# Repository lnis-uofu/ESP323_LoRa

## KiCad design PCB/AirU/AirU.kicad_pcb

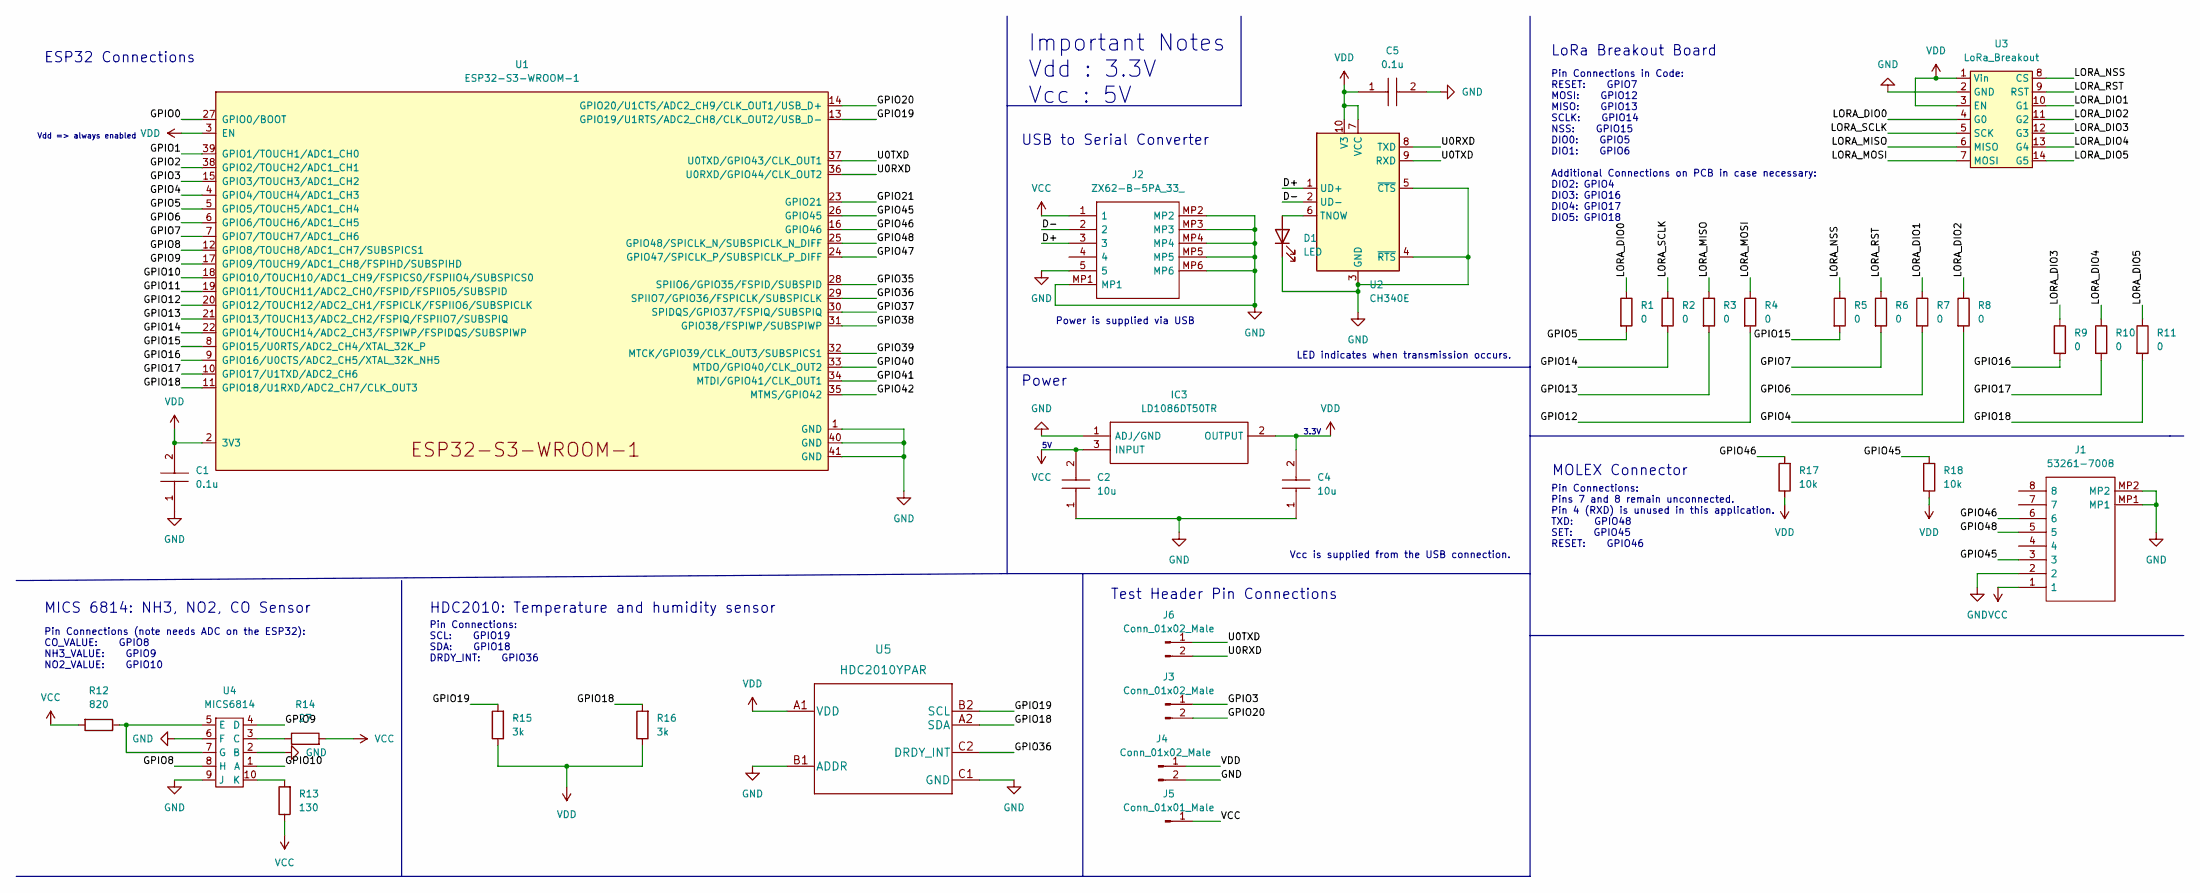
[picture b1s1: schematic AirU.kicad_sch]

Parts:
C1: 0.1u; CAPC1608X94N; Mouser Part Number 581-0603YC105KAT2A
C2, C4: 10u; CAPC1608X90N; Mouser Part Number 581-0603ZD106KAT2A
C5: 0.1u; CAPC1608X90N; Mouser Part Number 581-0603YC104J4T4A
D1: LED; LED_0603_1608Metric
IC3: LD1086DT50TR; LD1086DT33TR; Mouser Part Number 511-LD1086DT50TR
J1: 53261-7008; 532617008; Mouser Part Number 538-53261-7008
J2: ZX62-B-5PA_33_; ZX62B5PA33; Mouser Part Number 798-ZX62-B-5PA33
J3, J4, J6: Conn_01x02_Male; PinHeader_1x02_P2.54mm_Vertical
J5: Conn_01x01_Male; PinHeader_1x01_P2.54mm_Vertical
R1, R2, R3, R4, R5, R6, R7, R8, R9, R10, R11: 0; R_0603_1608Metric
R12: 820; R_0603_1608Metric
R13: 130; R_0603_1608Metric
R14: 27; R_0603_1608Metric
R15, R16: 3k; R_0603_1608Metric
R17, R18: 10k; R_0603_1608Metric
U1: ESP32-S3-WROOM-1
U2: CH340E; MSOP-10_3x3mm_P0.5mm
U3: LoRa_Breakout
U4: MICS6814; PLCC125P750X550X150-16N
U5: HDC2010YPAR

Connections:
/D+: J2.3, U2.1 (UD+)
/D-: J2.2, U2.2 (UD-)
/GPIO0: U1.27 (GPIO0/BOOT)
/GPIO1: U1.39 (GPIO1/TOUCH1/ADC1_CH0)
/GPIO2: U1.38 (GPIO2/TOUCH2/ADC1_CH1)
/GPIO3: J3.1, U1.15 (GPIO3/TOUCH3/ADC1_CH2)
/GPIO4: R8.2, U1.4 (GPIO4/TOUCH4/ADC1_CH3)
/GPIO5: R1.2, U1.5 (GPIO5/TOUCH5/ADC1_CH4)
/GPIO6: R7.2, U1.6 (GPIO6/TOUCH6/ADC1_CH5)
/GPIO7: R6.2, U1.7 (GPIO7/TOUCH7/ADC1_CH6)
/GPIO8: U1.12 (GPIO8/TOUCH8/ADC1_CH7/SUBSPICS1), U4.8 (H)
/GPIO9: U1.17 (GPIO9/TOUCH9/ADC1_CH8/FSPIHD/SUBSPIHD), U4.4 (D)
/GPIO10: U1.18 (GPIO10/TOUCH10/ADC1_CH9/FSPICS0/FSPIIO4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), U4.1 (A)
/GPIO11: U1.19 (GPIO11/TOUCH11/ADC2_CH0/FSPID/FSPIIO5/S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)
/GPIO12: R4.2, U1.20 (GPIO12/TOUCH12/ADC2_CH1/FSPICLK/FSPIIO6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)
/GPIO13: R3.2, U1.21 (GPIO13/TOUCH13/ADC2_CH2/FSPIQ/FSPIIO7/S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)
/GPIO14: R2.2, U1.22 (GPIO14/TOUCH14/ADC2_CH3/FSPIWP/FSPIDQS/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)
/GPIO15: R5.2, U1.8 (GPIO15/U0RTS/ADC2_CH4/XTAL_32K_P)
/GPIO16: R9.2, U1.9 (GPIO16/U0CTS/ADC2_CH5/XTAL_32K_NH5)
/GPIO17: R10.2, U1.10 (GPIO17/U1TXD/ADC2_CH6)
/GPIO18: R11.2, R16.2, U1.11 (GPIO18/U1RXD/ADC2_CH7/CLK_OUT3), U5.A2 (SDA)
/GPIO19: R15.2, U1.13 (GPIO19/U1RTS/ADC2_CH8/CLK_OUT2/USB_D-), U5.B2 (SCL)
/GPIO20: J3.2, U1.14 (GPIO20/U1CTS/ADC2_CH9/CLK_OUT1/USB_D+)
/GPIO21: U1.23 (GPIO21)
/GPIO35: U1.28 (SPIIO6/GPIO35/FSPID/SUBSPID)
/GPIO36: U1.29 (SPIIO7/GPIO36/FSPICLK/SUBSPICLK), U5.C2 (DRDY_INT)
/GPIO37: U1.30 (SPIDQS/GPIO37/FSPIQ/SUBSPIQ)
/GPIO38: U1.31 (GPIO38/FSPIWP/SUBSPIWP)
/GPIO39: U1.32 (MTCK/GPIO39/CLK_OUT3/SUBSPICS1)
/GPIO40: U1.33 (MTDO/GPIO40/CLK_OUT2)
/GPIO41: U1.34 (MTDI/GPIO41/CLK_OUT1)
/GPIO42: U1.35 (MTMS/GPIO42)
/GPIO45: J1.3, R18.2, U1.26 (GPIO45)
/GPIO46: J1.6, R17.2, U1.16 (GPIO46)
/GPIO47: U1.24 (GPIO47/SPICLK_P/SUBSPICLK_P_DIFF)
/GPIO48: J1.5, U1.25 (GPIO48/SPICLK_N/SUBSPICLK_N_DIFF)
/LORA_DIO0: R1.1, U3.4 (G0)
/LORA_DIO1: R7.1, U3.10 (G1)
/LORA_DIO2: R8.1, U3.11 (G2)
/LORA_DIO3: R9.1, U3.12 (G3)
/LORA_DIO4: R10.1, U3.13 (G4)
/LORA_DIO5: R11.1, U3.14 (G5)
/LORA_MISO: R3.1, U3.6 (MISO)
/LORA_MOSI: R4.1, U3.7 (MOSI)
/LORA_NSS: R5.1, U3.8 (CS)
/LORA_RST: R6.1, U3.9 (RST)
/LORA_SCLK: R2.1, U3.5 (SCK)
/U0RXD: J6.2, U1.36 (U0RXD/GPIO44/CLK_OUT2), U2.8 (TXD)
/U0TXD: J6.1, U1.37 (U0TXD/GPIO43/CLK_OUT1), U2.9 (RXD)
GND: C1.1, C2.1, C4.1, C5.2, D1.1 (K), IC3.1 (ADJ/GND), J1.2, J1.MP1, J1.MP2, J2.5, J2.MP1, J2.MP2, J2.MP3, J2.MP4, J2.MP5, J2.MP6, J4.2, U1.1 (GND), U1.40 (GND), U1.41 (GND), U2.3 (GND), U2.4 (~RTS), U2.5 (~CTS), U3.2 (GND), U4.2 (B), U4.6 (F), U4.9 (J), U5.B1 (ADDR), U5.C1 (GND)
unnamed: D1.2 (A), U2.6 (TNOW)
unnamed: R12.1, U4.5 (E), U4.7 (G)
unnamed: R13.2, U4.10 (K)
unnamed: R14.1, U4.3 (C)
VCC: C2.2, IC3.3 (INPUT), J1.1, J2.1, J5.1, R12.2, R13.1, R14.2
VDD: C1.2, C4.2, C5.1, IC3.2 (OUTPUT), J4.1, R15.1, R16.1, R17.1, R18.1, U1.2 (3V3), U1.3 (EN), U2.7 (VCC), U2.10 (V3), U3.1 (Vin), U3.3 (EN), U5.A1 (VDD)

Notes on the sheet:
LoRa Breakout Board
Pin Connections in Code: RESET: GPIO7 MOSI: GPIO12 MISO: GPIO13 SCLK: GPIO14 NSS: GPIO15 DIO0: GPIO5 DIO1: GPIO6 Additional Connections on PCB in case necessary: DIO2: GPIO4 DIO3: GPIO16 DIO4: GPIO17 DIO5: GPIO18
Vcc is supplied from the USB connection.
HDC2010: Temperature and humidity sensor
MOLEX Connector
Pin Connections: SCL: GPIO19 SDA: GPIO18 DRDY_INT: GPIO36
Vdd => always enabled
USB to Serial Converter
LED indicates when transmission occurs.
Important Notes Vdd : 3.3V Vcc : 5V
Test Header Pin Connections
MICS 6814: NH3, NO2, CO Sensor
Pin Connections (note needs ADC on the ESP32): CO_VALUE: GPIO8 NH3_VALUE: GPIO9 NO2_VALUE: GPIO10
Power is supplied via USB
3.3V
ESP32 Connections
Pin Connections: Pins 7 and 8 remain unconnected. Pin 4 (RXD) is unused in this application. TXD: GPIO48 SET: GPIO45 RESET: GPIO46
Power

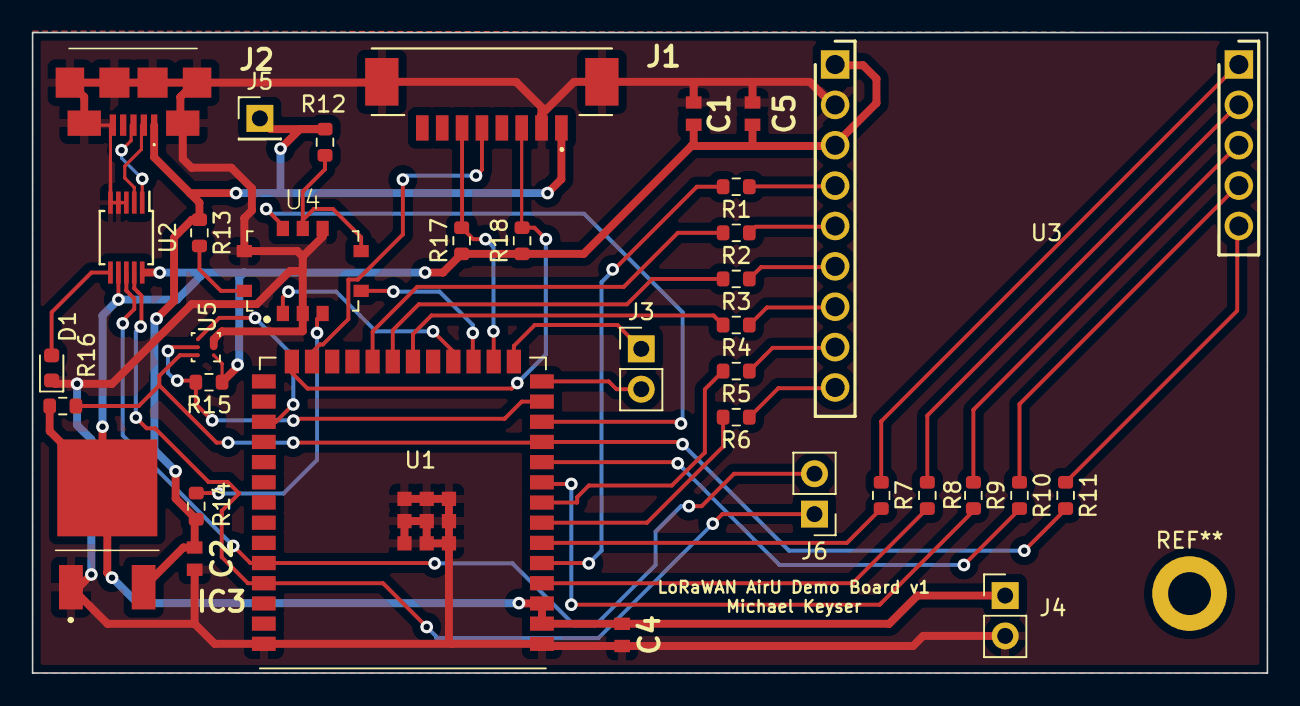
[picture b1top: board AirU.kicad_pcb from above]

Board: 2 copper layers, 77.7 x 40.3 mm, 35 parts (0 on the bottom side), 43 nets.

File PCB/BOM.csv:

"Id";"Designator";"Package";"Quantity";"Designation";"Supplier and ref";
1;"R5,R8,R9,R3,R2,R7,R6,R10,R4,R1,R11";"R_0603_1608Metric";11;"0";;;
2;"R14";"R_0603_1608Metric";1;"27";;;
3;"J6,J4,J3";"PinHeader_1x02_P2.54mm_Vertical";3;"Conn_01x02_Male";;;
4;"U1";"ESP32-S3-WROOM-1";1;"ESP32-S3-WROOM-1";;;
5;"R17,R18";"R_0603_1608Metric";2;"10k";;;
6;"C4,C2";"CAPC1608X90N";2;"10u";;;
7;"U5";"HDC2010YPAR";1;"HDC2010YPAR";;;
8;"R15,R16";"R_0603_1608Metric";2;"3k";;;
9;"D1";"LED_0603_1608Metric";1;"LED";;;
10;"IC3";"LD1086DT33TR";1;"LD1086DT50TR";;;
11;"C1";"CAPC1608X94N";1;"0.1u";;;
12;"U4";"PLCC125P750X550X150-16N";1;"MICS6814";;;
13;"R13";"R_0603_1608Metric";1;"130";;;
14;"J5";"PinHeader_1x01_P2.54mm_Vertical";1;"Conn_01x01_Male";;;
15;"U3";"LoRa_Breakout";1;"LoRa_Breakout";;;
16;"U2";"MSOP-10_3x3mm_P0.5mm";1;"CH340E";;;
17;"R12";"R_0603_1608Metric";1;"820";;;
18;"J2";"ZX62B5PA33";1;"ZX62-B-5PA_33_";;;
19;"J1";"532617008";1;"53261-7008";;;
20;"C5";"CAPC1608X90N";1;"0.1u";;;

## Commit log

2022-06-06 Setup .gitignore
2022-06-06 setting up project
2022-06-06 setting up lora
2022-06-06 updating .gitignroe
2022-06-06 removing .DS-Store
2022-06-07 LoRa sending functional
2022-06-07 Sending and receiving using the LoRa library is working
2022-06-07 organizing repo
2022-06-08 testing lora
2022-06-09 working to make led blink when a message is received
2022-06-10 blink led when message received using a mutex
2022-06-15 got build working for stm32
2022-06-16 have FreeRTOS on the stm32 working
2022-06-16 working on getting lorawan to work
2022-06-16 working on lorawan
2022-06-17 working on lorawn
2022-06-17 organizing freertos and lorawan code
2022-06-17 organizing lorawan
2022-06-17 FreeRTOS is working
2022-06-21 freertos working, going to work on lorawan now
2022-06-22 added LoRaMac-node to repo
2022-06-22 fixing repo
2022-06-22 add LoRaMac-node manually, not using git clone or git submodule
2022-06-22 organized LoRa node component for esp
2022-06-22 added license from semtech
2022-06-23 removing LoRaMac node to setup as submodule
2022-06-23 LoRaMAC node setup as submodule
2022-06-23 LoRaMac-node building successfully
2022-06-27 added pseudocode for LoRaWAN testing
2022-06-27 updated pseudocode
2022-06-28 getting lorawan to build on ESP32
2022-06-28 working on ping pong example
2022-06-29 successfully build after changing some pins and basic function implementations
2022-06-30 working on setting up GPIOs
2022-06-30 integrating gpio interfaces
2022-07-02 working on implementing GPIOs
2022-07-04 working on GPIOs
2022-07-05 gpio interface almost complete
2022-07-07 working on getting library to work with board
2022-07-07 testing gpio functions
2022-07-07 gpio works when testing independently with LED
2022-07-08 going back to working version
2022-07-08 updating branch before switching
2022-07-08 pushing before new branch
2022-07-08 working on lora debugging
2022-07-12 verified spi working with single hardcoded character
2022-07-13 working on lora setup
2022-07-14 debugging radio init code
2022-07-14 working on implementing critical sections
2022-07-18 committing after resetting
2022-07-19 debugger setup and reaching sending loop
2022-07-20 setup logic analyzer to monitor send with working LoRa code, turned the SPI clock freq down
2022-07-20 starting to debug lorawan send
2022-07-25 successfully sending a byte using LoRaWAN API
2022-07-28 setup rtc-board code to interface with RTC
2022-07-29 configured debugging specific for this project
2022-07-29 fixed debugging settings
2022-08-02 added error checking to gpios
2022-08-02 sending and receiving works, interrupts are setup properly
2022-08-02 cleanup after merge
2022-08-02 working on getting lorawan to build
2022-08-03 put in dummy functions, project now builds
2022-08-04 added encryption files
2022-08-16 implemented eeprom code using regular flash memory
2022-08-17 entire project builds and does not abort()
2022-08-17 added dev eui and other keys for connecting to network
2022-09-03 debugging send
2022-09-03 debuggin join procedure
2022-09-09 Test_LoRa and Test_LoRa_Receive successfully send data to the gateway
2022-09-10 sending data to the gateway, changed the frequency
2022-10-20 updating debugging changes
2022-10-20 created new branch for pcb work and added gitignore for kicad
2022-10-20 added espressif pcb library
2022-10-27 setup parts libraries
2022-11-01 usb to serial done on schematic
2022-11-01 added footprint for lora breakout board
2022-11-04 added most parts to pcb
2022-11-08 schematic complete
2022-11-08 part of layout done
2022-11-08 pcb layout complete
2022-12-14 final update before ownership transfer

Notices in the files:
parts and their libraries:
Copyright 2021 Accelerated Designs. All rights reserved.
